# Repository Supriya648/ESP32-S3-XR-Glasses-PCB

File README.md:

# ESP32-S3-XR-Glasses-PCB
Custom PCB with ESP32-S3 camera module for AI/XR glasses
# ESP32-S3 Camera Resolution Performance Demo

## Project Overview
This project demonstrates video capture using an ESP32-S3-based camera system at multiple
resolutions to study trade-offs between image quality, frame rate, and memory usage.
The system is intended for compact, wearable AI/XR applications.

## Hardware
- ESP32-S3 MCU
- Camera module (OV2640 / OV3660)
- External PSRAM (on-chip)
- USB power and programming interface

## Software
- Arduino framework
- ESP32 camera driver

## Demo Description
Video clips were captured at different resolutions supported by the ESP32-S3:
- 320×240 (QVGA)
- 640×480 (VGA)
- 800×600 (SVGA)

Each configuration was evaluated for visual quality and approximate frame rate.

## Results
Lower resolutions achieved higher frame rates and stability, while higher resolutions
provided improved image detail at the cost of increased memory usage and reduced frame rate.

## Repository Structure
- firmware/: ESP32-S3 camera firmware
- hardware/: Schematic and PCB layout
- results/: Recorded video samples and performance logs
- report/: Final project report (PDF)

## Demo Video
YouTube link: [https://youtu.be/lZMv0Ex0UyA]

## Author
Supriya Ramaswamy  
EECE – Wireless & Network Engineering

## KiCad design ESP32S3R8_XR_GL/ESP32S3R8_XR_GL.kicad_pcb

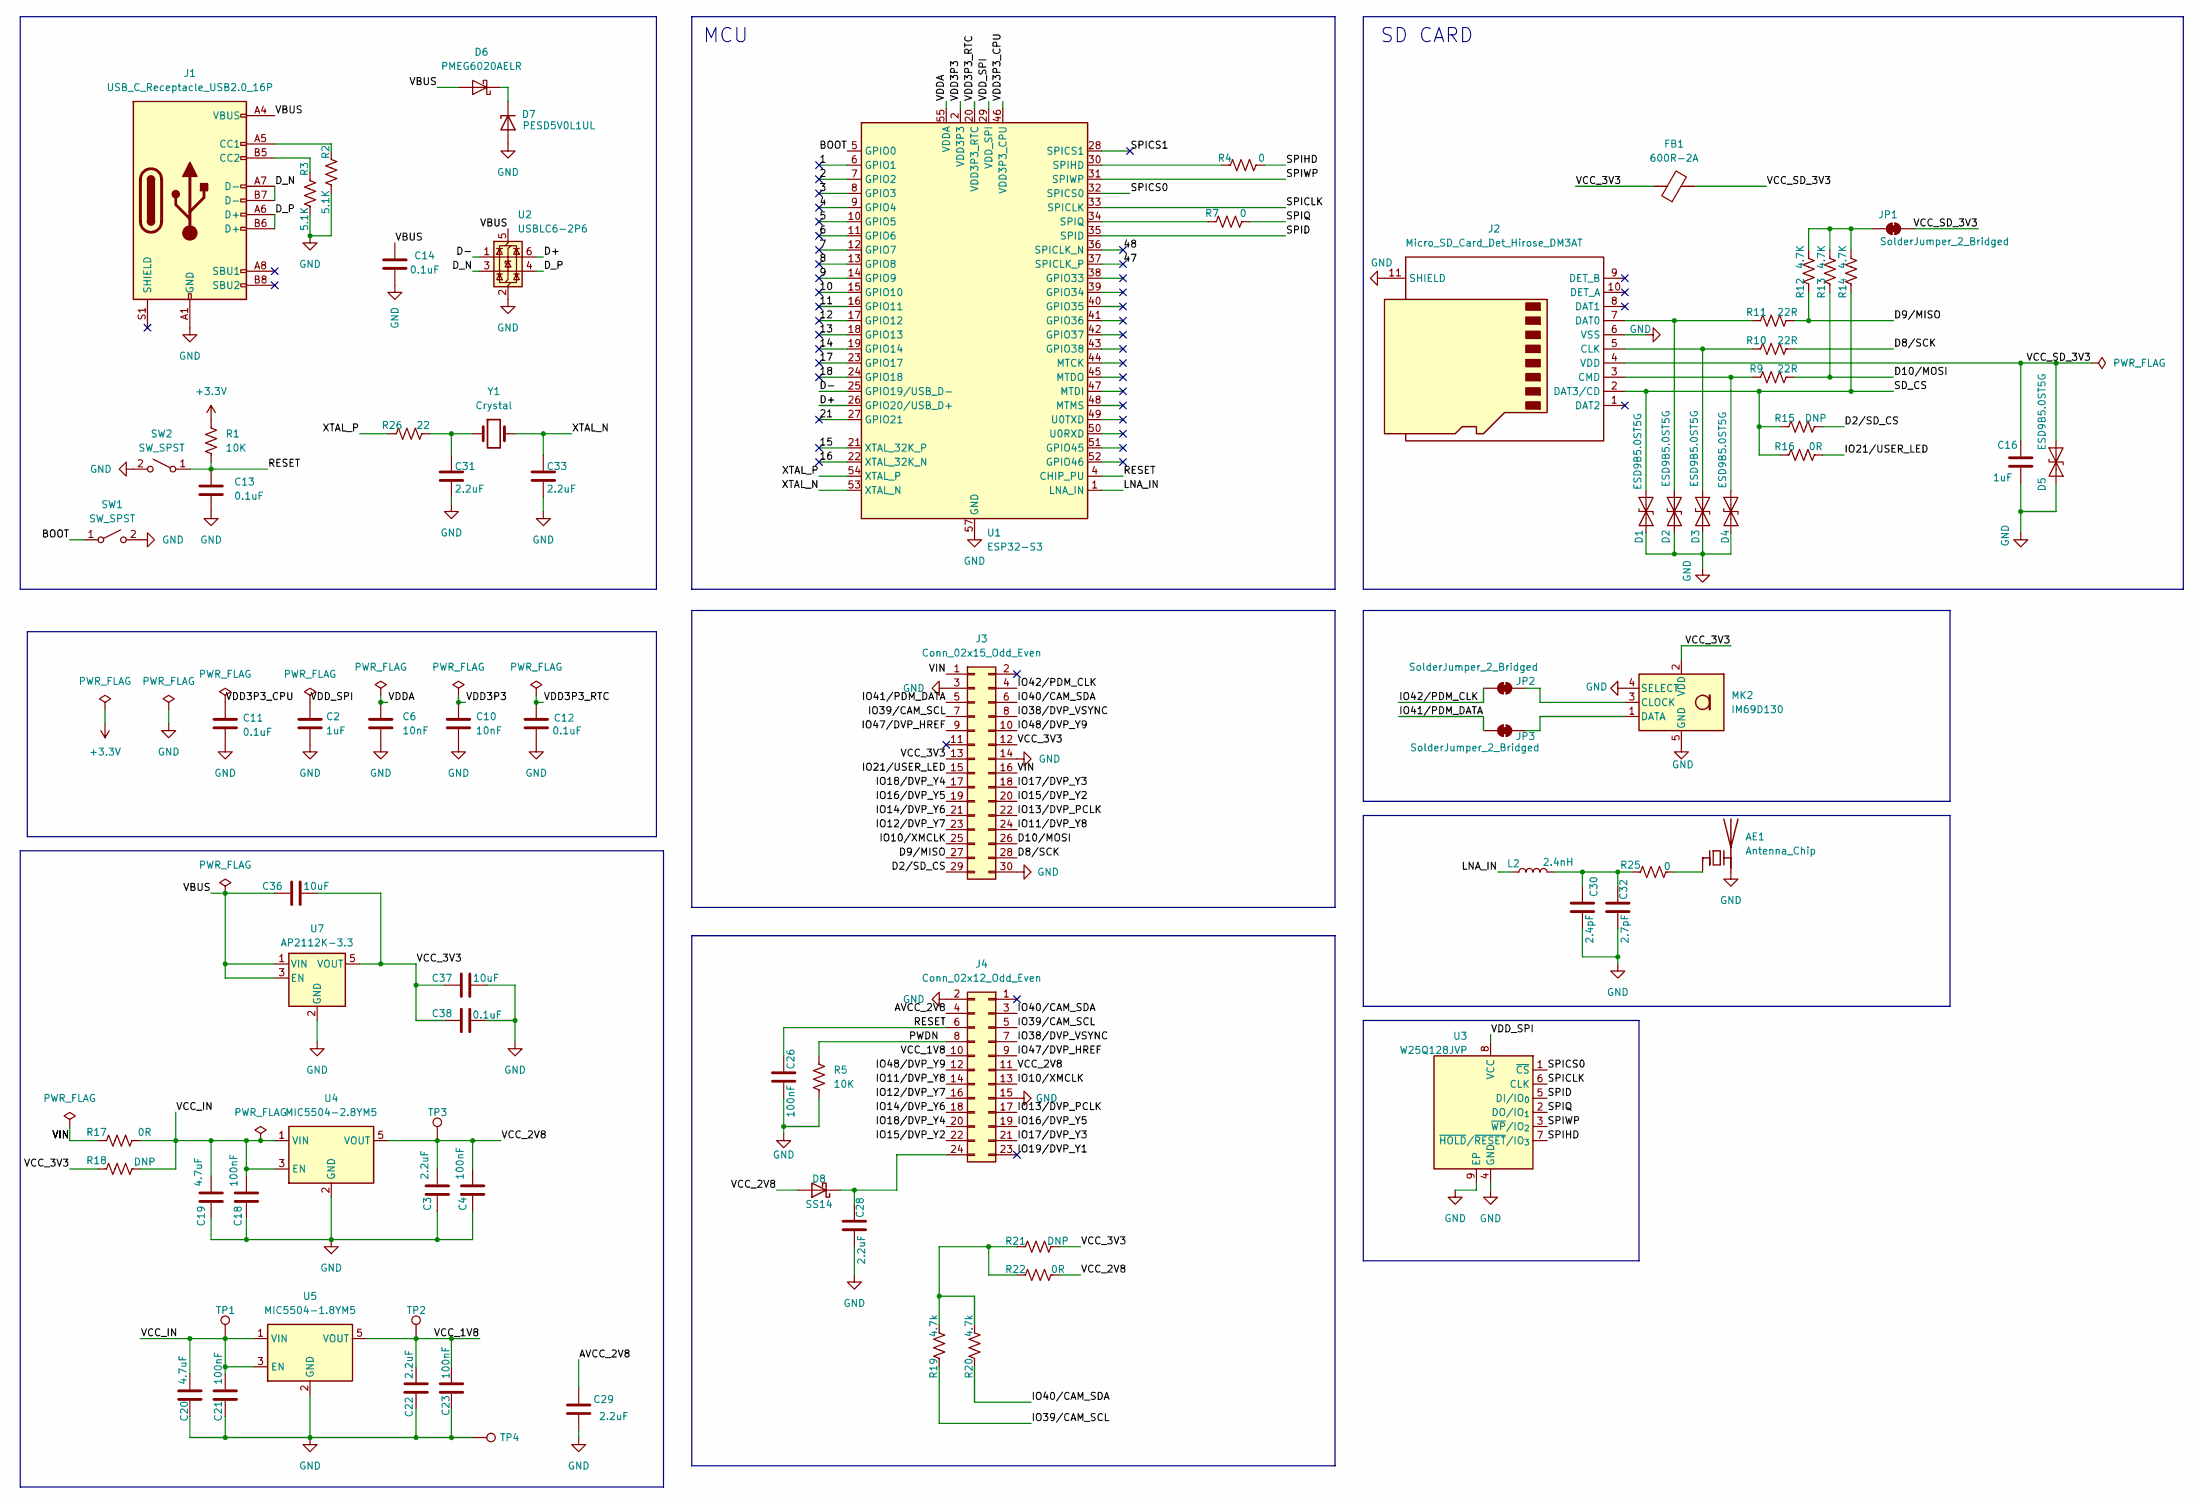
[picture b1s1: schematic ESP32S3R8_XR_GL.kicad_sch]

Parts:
AE1: Antenna_Chip; Johanson_2450AT18x100
C2, C16: 1uF; C_0603_1608Metric
C3, C22, C28, C29, C31, C33: 2.2uF; C_0603_1608Metric
C4, C18, C21, C23, C26: 100nF; C_0402_1005Metric
C6, C10: 10nF; C_0402_1005Metric
C11, C12, C13, C14, C38: 0.1uF; C_0402_1005Metric
C19, C20: 4.7uF; C_0603_1608Metric
C30: 2.4pF; C_0402_1005Metric
C32: 2.7pF; C_0402_1005Metric
C36, C37: 10uF; C_0805_2012Metric
D1, D2, D3, D4, D5: ESD9B5.0ST5G; D_SOD-923
D6: PMEG6020AELR; Nexperia_CFP3_SOD-123W
D7: PESD5V0L1UL; D_SOD-882
D8: SS14; D_SMA
FB1: 600R-2A; L_0805_2012Metric
J1: USB_C_Receptacle_USB2.0_16P; USB_C_Receptacle_GCT_USB4085
J2: Micro_SD_Card_Det_Hirose_DM3AT; microSD_HC_Hirose_DM3AT-SF-PEJM5
J3: Conn_02x15_Odd_Even; PinHeader_2x15_P2.54mm_Vertical
J4: Conn_02x12_Odd_Even; PinHeader_2x12_P2.54mm_Vertical
JP1, JP2, JP3: SolderJumper_2_Bridged; SolderJumper-2_P1.3mm_Bridged_RoundedPad1.0x1.5mm
L2: 2.4nH; L_0402_1005Metric
MK2: IM69D130; Infineon_PG-LLGA-5-1
R1, R5: 10K; R_0402_1005Metric
R2, R3: 5.1K; R_0402_1005Metric
R4, R7, R25: 0; R_0402_1005Metric
R9, R10, R11: 22R; R_0402_1005Metric
R12, R13, R14: 4.7K; R_0402_1005Metric
R15, R18, R21: DNP; R_0402_1005Metric
R16, R17, R22: 0R; R_0402_1005Metric
R19, R20: 4.7k; R_0402_1005Metric
R26: 22; R_0402_1005Metric
SW1, SW2: SW_SPST; SW_SPST_SKQG_WithStem
TP1, TP2, TP3, TP4: TestPoint; TestPoint_Pad_D1.0mm
U1: ESP32-S3; QFN-56-1EP_7x7mm_P0.4mm_EP4x4mm
U2: USBLC6-2P6; SOT-666
U3: W25Q128JVP; WSON-8-1EP_6x5mm_P1.27mm_EP3.4x4.3mm
U4: MIC5504-2.8YM5; SOT-23-5
U5: MIC5504-1.8YM5; SOT-23-5
U7: AP2112K-3.3; SOT-23-5
Y1: Crystal; Crystal_SMD_3225-4Pin_3.2x2.5mm

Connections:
+3.3V: R1.1
/1: U1.6 (GPIO1)
/2: U1.7 (GPIO2)
/3: U1.8 (GPIO3)
/4: U1.9 (GPIO4)
/5: U1.10 (GPIO5)
/6: U1.11 (GPIO6)
/7: U1.12 (GPIO7)
/8: U1.13 (GPIO8)
/9: U1.14 (GPIO9)
/10: U1.15 (GPIO10)
/11: U1.16 (GPIO11)
/12: U1.17 (GPIO12)
/13: U1.18 (GPIO13)
/14: U1.19 (GPIO14)
/15: U1.21 (XTAL_32K_P)
/16: U1.22 (XTAL_32K_N)
/17: U1.23 (GPIO17)
/18: U1.24 (GPIO18)
/21: U1.27 (GPIO21)
/47: U1.37 (SPICLK_P)
/48: U1.36 (SPICLK_N)
/AVCC_2V8: C29.1, J4.4
/BOOT: SW1.1 (A), U1.5 (GPIO0)
/D2/SD_CS: J3.29, R15.2
/D8/SCK: J3.28, R10.2
/D9/MISO: J3.27, R11.2, R12.1
/D10/MOSI: J3.26, R9.2, R13.1
/D+: U1.26 (GPIO20/USB_D+), U2.6 (I/O1)
/D-: U1.25 (GPIO19/USB_D-), U2.1 (I/O1)
/D_N: J1.A7 (D-), J1.B7 (D-), U2.3 (I/O2)
/D_P: J1.A6 (D+), J1.B6 (D+), U2.4 (I/O2)
/IO10/XMCLK: J3.25, J4.13
/IO11/DVP_Y8: J3.24, J4.14
/IO12/DVP_Y7: J3.23, J4.16
/IO13/DVP_PCLK: J3.22, J4.17
/IO14/DVP_Y6: J3.21, J4.18
/IO15/DVP_Y2: J3.20, J4.22
/IO16/DVP_Y5: J3.19, J4.19
/IO17/DVP_Y3: J3.18, J4.21
/IO18/DVP_Y4: J3.17, J4.20
/IO19/DVP_Y1: J4.23
/IO21/USER_LED: J3.15, R16.2
/IO38/DVP_VSYNC: J3.8, J4.7
/IO39/CAM_SCL: J3.7, J4.5, R19.1
/IO40/CAM_SDA: J3.6, J4.3, R20.1
/IO41/PDM_DATA: J3.5, JP3.2 (B)
/IO42/PDM_CLK: J3.4, JP2.2 (B)
/IO47/DVP_HREF: J3.9, J4.9
/IO48/DVP_Y9: J3.10, J4.12
/LNA_IN: L2.1, U1.1 (LNA_IN)
/PWDN: J4.8, R5.1
/RESET: C13.1, C26.1, J4.6, R1.2, SW2.1 (A), U1.4 (CHIP_PU)
/SD_CS: D1.2 (A2), J2.2 (DAT3/CD), R14.1, R15.1, R16.1
/SPICLK: U1.33 (SPICLK), U3.6 (CLK)
/SPICS0: U1.32 (SPICS0), U3.1 (~CS)
/SPICS1: U1.28 (SPICS1)
/SPID: U1.35 (SPID), U3.5 (DI/IO_{0})
/SPIHD: R4.2, U3.7 (~HOLD/~RESET/IO_{3})
/SPIQ: R7.2, U3.2 (DO/IO_{1})
/SPIWP: U1.31 (SPIWP), U3.3 (~WP/IO_{2})
/VBUS: C14.1, C36.1, D6.2 (A), J1.A4 (VBUS), J1.A9 (VBUS), J1.B4 (VBUS), J1.B9 (VBUS), U2.5 (VBUS), U7.1 (VIN), U7.3 (EN)
/VCC_1V8: C22.1, C23.1, J4.10, TP2.1, U5.5 (VOUT)
/VCC_2V8: C3.1, C4.1, D8.2 (A), J4.11, R22.2, TP3.1, U4.5 (VOUT)
/VCC_3V3: C36.2, C37.1, C38.1, FB1.1, J3.12, J3.13, MK2.2 (VDD), R18.1, R21.2, U7.5 (VOUT)
/VCC_IN: C18.1, C19.1, C20.1, C21.1, R17.2, R18.2, TP1.1, U4.1 (VIN), U4.3 (EN), U5.1 (VIN), U5.3 (EN)
/VCC_SD_3V3: C16.1, D5.2 (A2), FB1.2, J2.4 (VDD), JP1.2 (B)
/VDD3P3: C10.1, U1.2 (VDD3P3), U1.3 (VDD3P3)
/VDD3P3_CPU: C11.1, U1.46 (VDD3P3_CPU)
/VDD3P3_RTC: C12.1, U1.20 (VDD3P3_RTC)
/VDDA: C6.1, U1.55 (VDDA), U1.56 (VDDA)
/VDD_SPI: C2.1, U1.29 (VDD_SPI), U3.8 (VCC)
/VIN: J3.1, J3.16, R17.1
/XTAL_N: C33.1, U1.53 (XTAL_N), Y1.2
/XTAL_P: R26.1, U1.54 (XTAL_P)
GND: AE1.2 (PCB_Trace), C2.2, C3.2, C4.2, C6.2, C10.2, C11.2, C12.2, C13.2, C14.2, C16.2, C18.2, C19.2, C20.2, C21.2, C22.2, C23.2, C26.2, C28.2, C29.2, C30.2, C31.2, C32.2, C33.2, C37.2, C38.2, D1.1 (A1), D2.1 (A1), D3.1 (A1), D4.1 (A1), D5.1 (A1), D7.2 (A), J1.A1 (GND), J1.A12 (GND), J1.B1 (GND), J1.B12 (GND), J2.6 (VSS), J2.11 (SHIELD), J3.3, J3.14, J3.30, J4.2, J4.15, MK2.4 (SELECT), MK2.5 (GND), R2.2, R3.2, R5.2, SW1.2 (B), SW2.2 (B), TP4.1, U1.57 (GND), U2.2 (GND), U3.4 (GND), U3.9 (EP), U4.2 (GND), U5.2 (GND), U7.2 (GND)
unnamed: AE1.1 (FEED), R25.1
unnamed: C30.1, C32.1, L2.2, R25.2
unnamed: C31.1, R26.2, Y1.1
unnamed: D2.2 (A2), J2.7 (DAT0), R11.1
unnamed: D3.2 (A2), J2.5 (CLK), R10.1
unnamed: D4.2 (A2), J2.3 (CMD), R9.1
unnamed: D6.1 (K), D7.1 (K)
unnamed: C28.1, D8.1 (K), J4.24
unnamed: J1.A5 (CC1), R2.1
unnamed: J1.B5 (CC2), R3.1
unnamed: JP1.1 (A), R12.2, R13.2, R14.2
unnamed: JP2.1 (A), MK2.3 (CLOCK)
unnamed: JP3.1 (A), MK2.1 (DATA)
unnamed: R19.2, R20.2, R21.1, R22.1
unnamed: R4.1, U1.30 (SPIHD)
unnamed: R7.1, U1.34 (SPIQ)

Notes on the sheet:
MCU
SD CARD

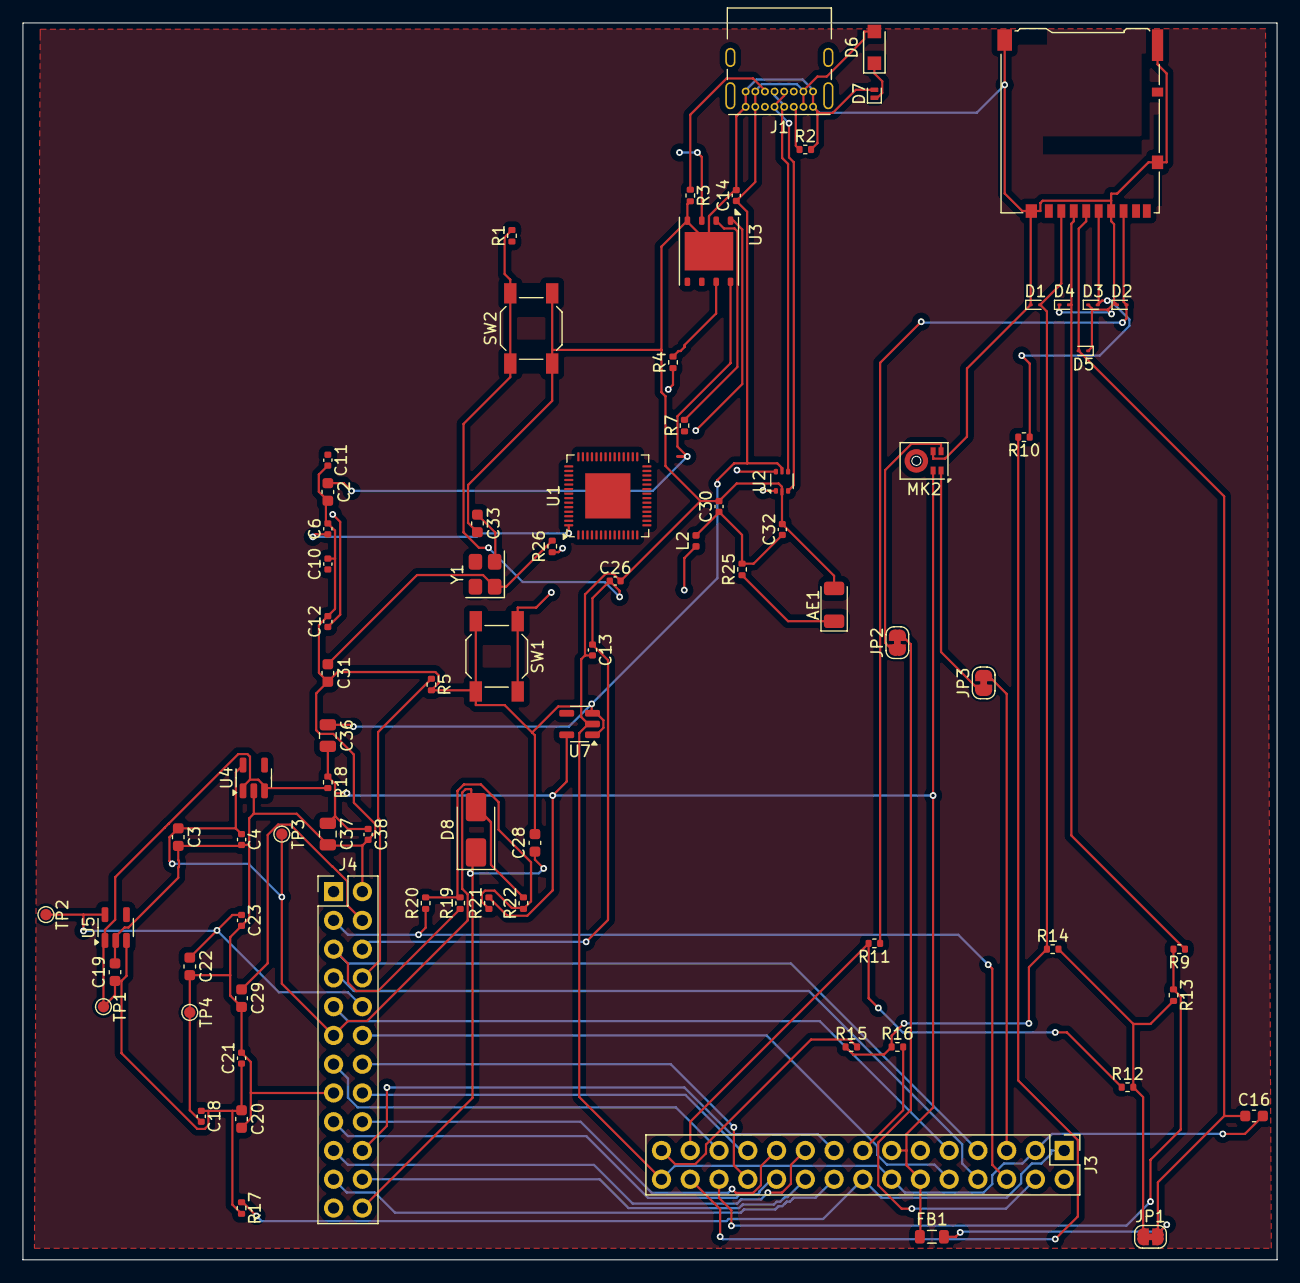
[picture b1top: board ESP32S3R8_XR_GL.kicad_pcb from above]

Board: 2 copper layers, 110.7 x 109.2 mm, 80 parts (0 on the bottom side), 68 nets.

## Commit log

2025-12-14 Expand README with project details and demo info
    Added project overview, hardware, software, demo details, results, repository structure, demo video link, and author information.
2025-12-14 Update README to remove firmware details
    Removed mention of custom firmware for camera resolution switching.
